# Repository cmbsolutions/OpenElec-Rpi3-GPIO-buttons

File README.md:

# OpenElec-Rpi3-GPIO-buttons
Add power buttons to the raspberry pi 3 running Openelec

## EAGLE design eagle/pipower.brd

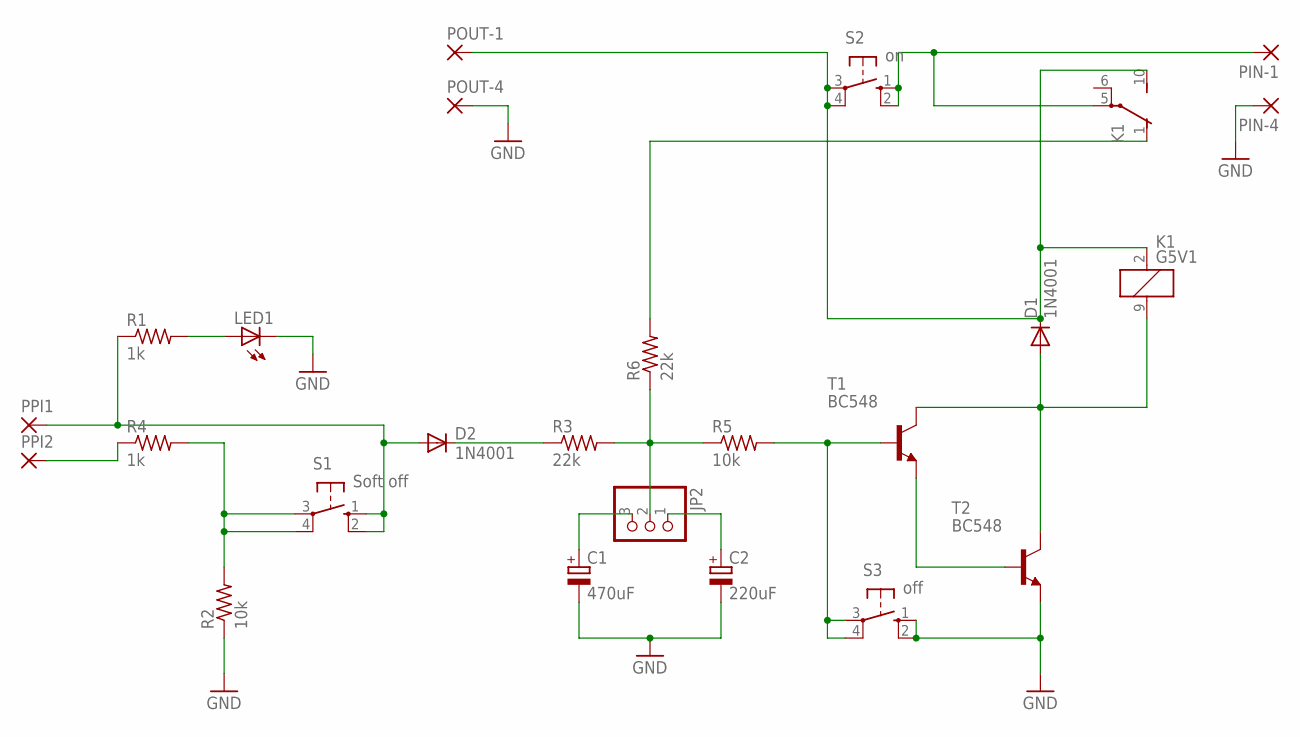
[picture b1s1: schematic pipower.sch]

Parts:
C1: 470uF; E2,5-7
C2: 220uF; E2,5-6
D1, D2: 1N4001; DO41-10
JP2: PINHD-1X3; 1X03
K1: G5V1
LED1: LED3MM
PIN-1, PIN-4: 2,54/1,0
POUT-1, POUT-4: 2,54/1,0
PPI1, PPI2: 2,54/1,0
R1, R4: 1k; 0207/7
R2, R5: 10k; 0207/7
R3, R6: 22k; 0207/7
S1: Soft off; B3F-10XX
S2: on; B3F-10XX
S3: off; B3F-10XX
T1, T2: BC548; TO92-CBE

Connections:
GND: C1.-, C2.-, LED1.K (C), PIN-4.1, POUT-4.1, R2.1, S3.1 (S), S3.2 (S1), T2.E
unnamed: PPI2.1, R4.1
unnamed: R2.2, R4.2, S1.3, S1.4 (P1)
unnamed: D2.C, R3.1
unnamed: JP2.2, R3.2, R5.1, R6.1
unnamed: LED1.A, R1.2
unnamed: D2.A, PPI1.1, R1.1, S1.1 (S), S1.2 (S1)
unnamed: R5.2, S3.3, S3.4 (P1), T1.B
unnamed: T1.E, T2.B
unnamed: D1.A, K1.9 (2), T1.C, T2.C
unnamed: D1.C, K1.2 (1), K1.10 (S), POUT-1.1, S2.3, S2.4 (P1)
unnamed: K1.1 (O), R6.2
unnamed: K1.5, PIN-1.1, S2.1 (S), S2.2 (S1)
unnamed: C2.+, JP2.1
unnamed: C1.+, JP2.3

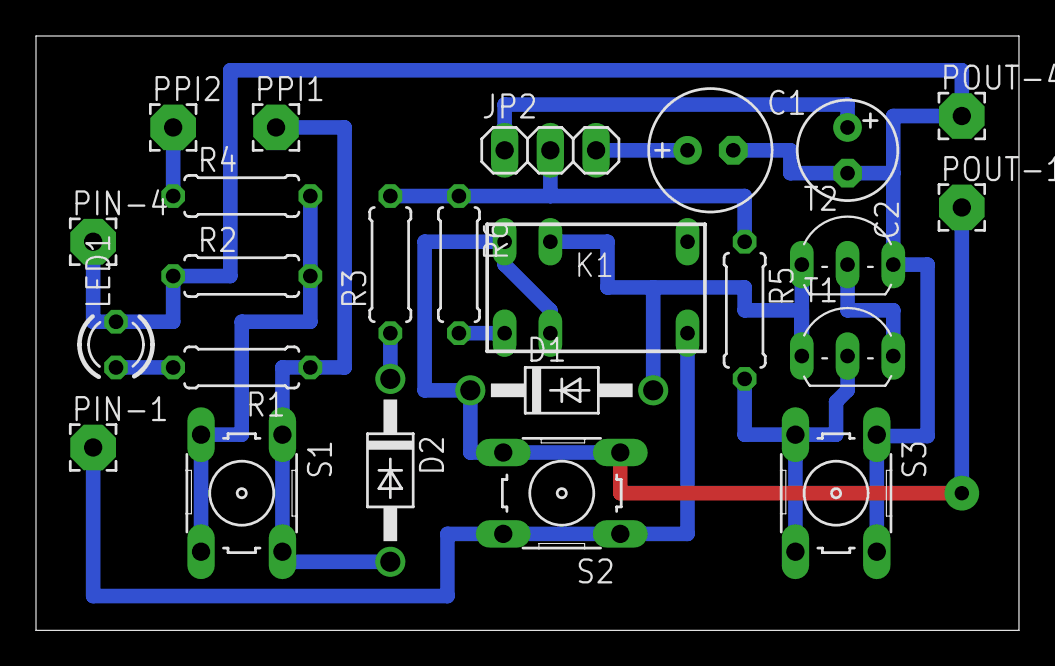
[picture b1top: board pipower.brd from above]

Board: 2 copper layers, 54.6 x 33.0 mm, 24 parts (0 on the bottom side), 15 nets.

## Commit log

2016-08-11 Eagle schematic and board files
2016-08-11 flatcam project and gcode files for cnc pcb milling
2016-08-11 Scripts to add to openelec
